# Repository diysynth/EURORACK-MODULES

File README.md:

# EURORACK-MODULES

Gerber files and schematics of various modules. For more information visit www.modwiggler.com/forum/viewtopic.php?t=262747

# List of Modules (so far)
- **3320 VCF** (6HP)
- **3340 VCO** (4HP)
- **ADSR ENVELOPE GENERATOR** (4HP)
- **BUFFERED MULTIPLE** (3HP)
- **CYCLING ENVELOPE GENERATOR** (4HP)
- **DIGILFO** (6HP, VCLFO)
- **DUAL VCA** (3HP, uses a LM13700 OTA)
- **LOOPING ATTACK/RELEASE ENVELOPE GENERATOR** (6HP)
- **NOISE LAB** (3HP)
- **OFFSET/GAIN UTILITY** (4HP)
- **PASSIVE LOW PASS GATE** (2HP)
- **POWER SUPPLY UNIT/MODULE** (6HP)
- **SUB MODULATOR** (6HP, advanced sub-oscillator)

# Coming soon(er or later)

- **Clock Divider module**

# License and additional Notes
Hardware designs and schematics are licensed under CC-BY-SA-4.0 (Sebastian Jazura - 2022-2025)

I can not give any warranties whatsoever and also can't be held responsible for any damages. You build this circuit at your own risk. If you can't verify on your own that those circuits are safe to use in your modular enviroment then please do not use them! If not stated otherwise I tested the basic functions of the circuits but I can't guarantee that they are bug-free. Please create an issue or a pull request if there is something wrong with one of the circuits.

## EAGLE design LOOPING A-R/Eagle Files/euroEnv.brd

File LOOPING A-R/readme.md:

# Looping Attack/Release Envelope Generator

* 6HP
* Switches for looping mode and time/range 
* Output CV: 0-10V (envelope mode); ~1-9V (looping mode)
* Manual trigger push button
* Only through-hole parts

*For more information see: https://www.modwiggler.com/forum/viewtopic.php?t=262747*

## Schematics:

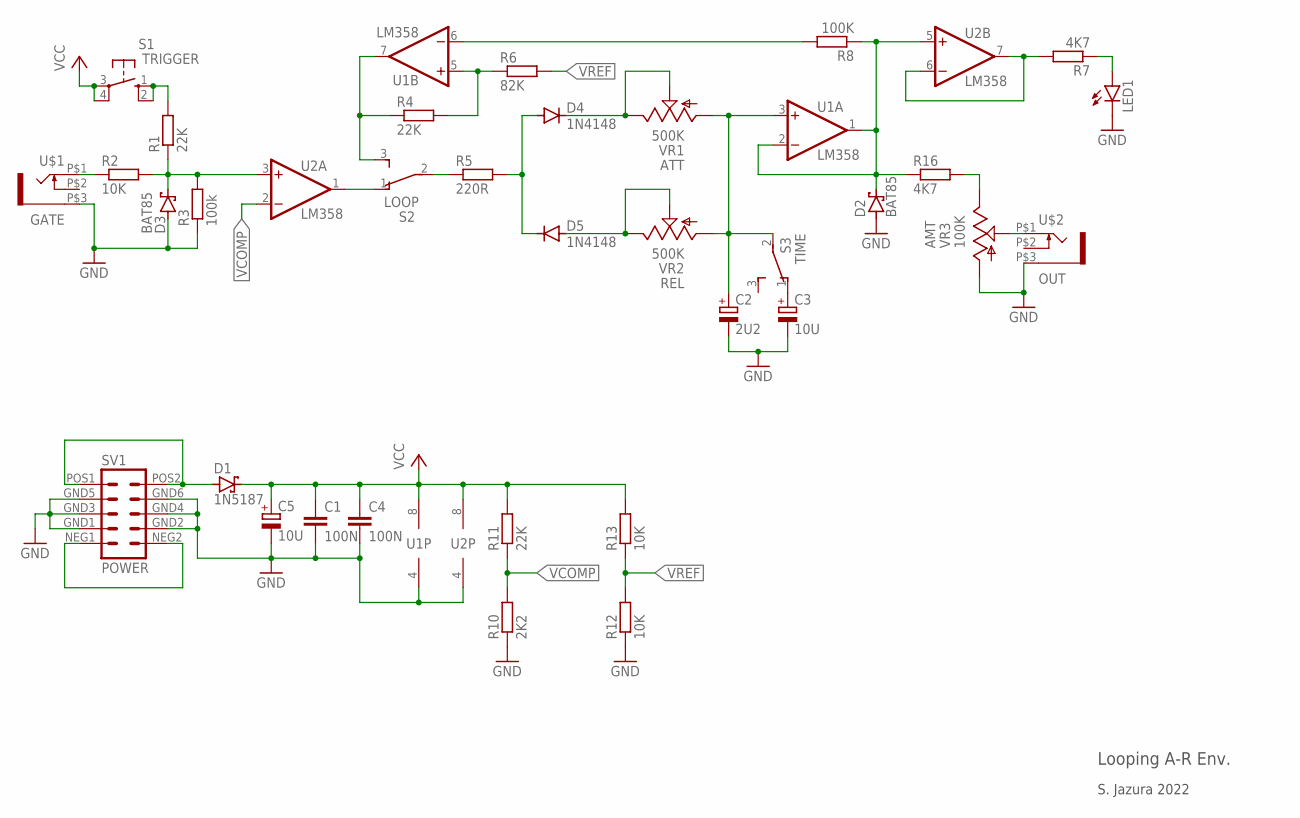
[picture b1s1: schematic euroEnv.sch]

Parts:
C1, C4: 100N; 000_7,5MM_FOIL_STANDARD
C2: 2U2; E2-5
C3, C5: 10U; E2-5
D1: 1N5187; 000_MOD_7MM_BAT_4148
D2, D3: BAT85; 000_MOD_7MM_BAT_4148
D4, D5: 1N4148; 000_MOD_7MM_BAT_4148
LED1: LED3MM
R1, R4, R11: 22K; 000_7,5MM_STANDARD
R2, R12, R13: 10K; 000_7,5MM_STANDARD
R3: 100k; 000_7,5MM_STANDARD
R5: 220R; 000_7,5MM_STANDARD
R6: 82K; 000_7,5MM_STANDARD
R7, R16: 4K7; 000_7,5MM_STANDARD
R8: 100K; 000_7,5MM_STANDARD
R10: 2K2; 000_7,5MM_STANDARD
S1: TRIGGER; D3R_CK_SWITCH
S2: LOOP; M9040P
S3: TIME; M9040P
SV1: POWER; EURO_PWR_HEADER_LOCK
U1, U2: LM358; DIL08
U$1: GATE; WQP-PJ301M-12_JACK
U$2: OUT; WQP-PJ301M-12_JACK
VR1, VR2: 500K; 9MM_SNAP-IN_POT
VR3: 100K; 9MM_SNAP-IN_POT

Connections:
GND: C1.2, C2.-, C3.-, C4.2, C5.-, D2.A, D3.A, LED1.K (C), R3.1, R10.1, R12.1, SV1.GND1 (4), SV1.GND2 (3), SV1.GND3 (6), SV1.GND4 (5), SV1.GND5 (8), SV1.GND6 (7), U1.4 (V-), U2.4 (V-), U$1.P$3 (1), U$2.P$3 (1), VR3.1 (A)
unnamed: D1.A, SV1.POS1 (10), SV1.POS2 (9)
unnamed: SV1.NEG1 (2), SV1.NEG2 (1)
unnamed: U$2.P$1 (2), VR3.2 (S)
unnamed: R16.2, VR3.3 (E)
unnamed: R7.2, U2.6 (-IN), U2.7 (OUT)
unnamed: LED1.A, R7.1
unnamed: D3.C, R1.1, R2.2, R3.2, U2.3 (+IN)
unnamed: R2.1, U$1.P$1 (2)
unnamed: R1.2, S1.1 (S), S1.2 (S1)
unnamed: S2.1 (O), U2.1 (OUT)
unnamed: R4.1, S2.3 (S), U1.7 (OUT)
unnamed: R5.1, S2.2
unnamed: D4.C, VR1.2 (S), VR1.3 (E)
unnamed: D4.A, D5.C, R5.2
unnamed: D5.A, VR2.2 (S), VR2.3 (E)
unnamed: C3.+, S3.1 (O)
unnamed: C2.+, S3.2, U1.3 (+IN), VR1.1 (A), VR2.1 (A)
unnamed: R4.2, R6.1, U1.5 (+IN)
unnamed: R8.2, U1.6 (-IN)
unnamed: D2.C, R8.1, R16.1, U1.1 (OUT), U1.2 (-IN), U2.5 (+IN)
VCC: C1.1, C4.1, C5.+, D1.C, R11.2, R13.2, S1.3, S1.4 (P1), U1.8 (V+), U2.8 (V+)
VCOMP: R10.2, R11.1, U2.2 (-IN)
VREF: R6.2, R12.2, R13.1

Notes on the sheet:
ATT
REL
AMT
S. Jazura 2022
Looping A-R Env.

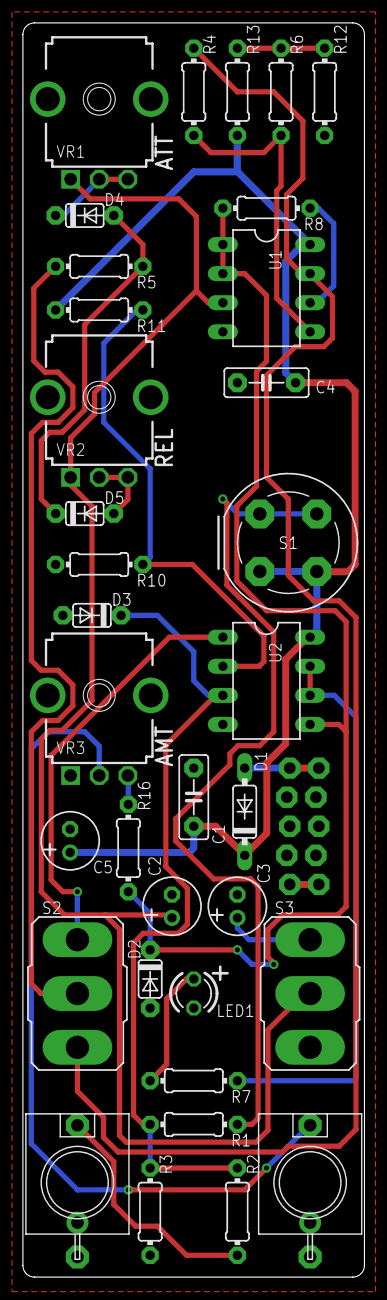
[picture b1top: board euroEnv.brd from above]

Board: 2 copper layers, 29.8 x 109.5 mm, 35 parts (1 on the bottom side), 24 nets.

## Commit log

2022-06-07 Create test
2022-06-07 Create rte
2022-06-07 Zipped Gerber Files
2022-06-07 Create ph
2022-06-07 Rename license.txt to license
2022-06-07 Create LICENSE
2022-06-29 Create empty
2022-11-28 Uploaded images
2022-11-28 Uploaded schematics
2022-11-28 Uploaded schematic
2022-11-28 Create re
2022-11-28 Create temp
2022-11-28 Uploaded Gerber Files
2022-11-28 Example image
2022-12-18 Add gerber files
2024-06-14 Create DIGILFO (6HP)
2024-07-14 Create temp
2024-07-15 Update LICENSE
